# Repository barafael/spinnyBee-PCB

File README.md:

# spinnyBee-PCB
Round PCB for dizzy little gyro on frisbee + WS2812 controlled by an Adafruit ItsyBitsy M4

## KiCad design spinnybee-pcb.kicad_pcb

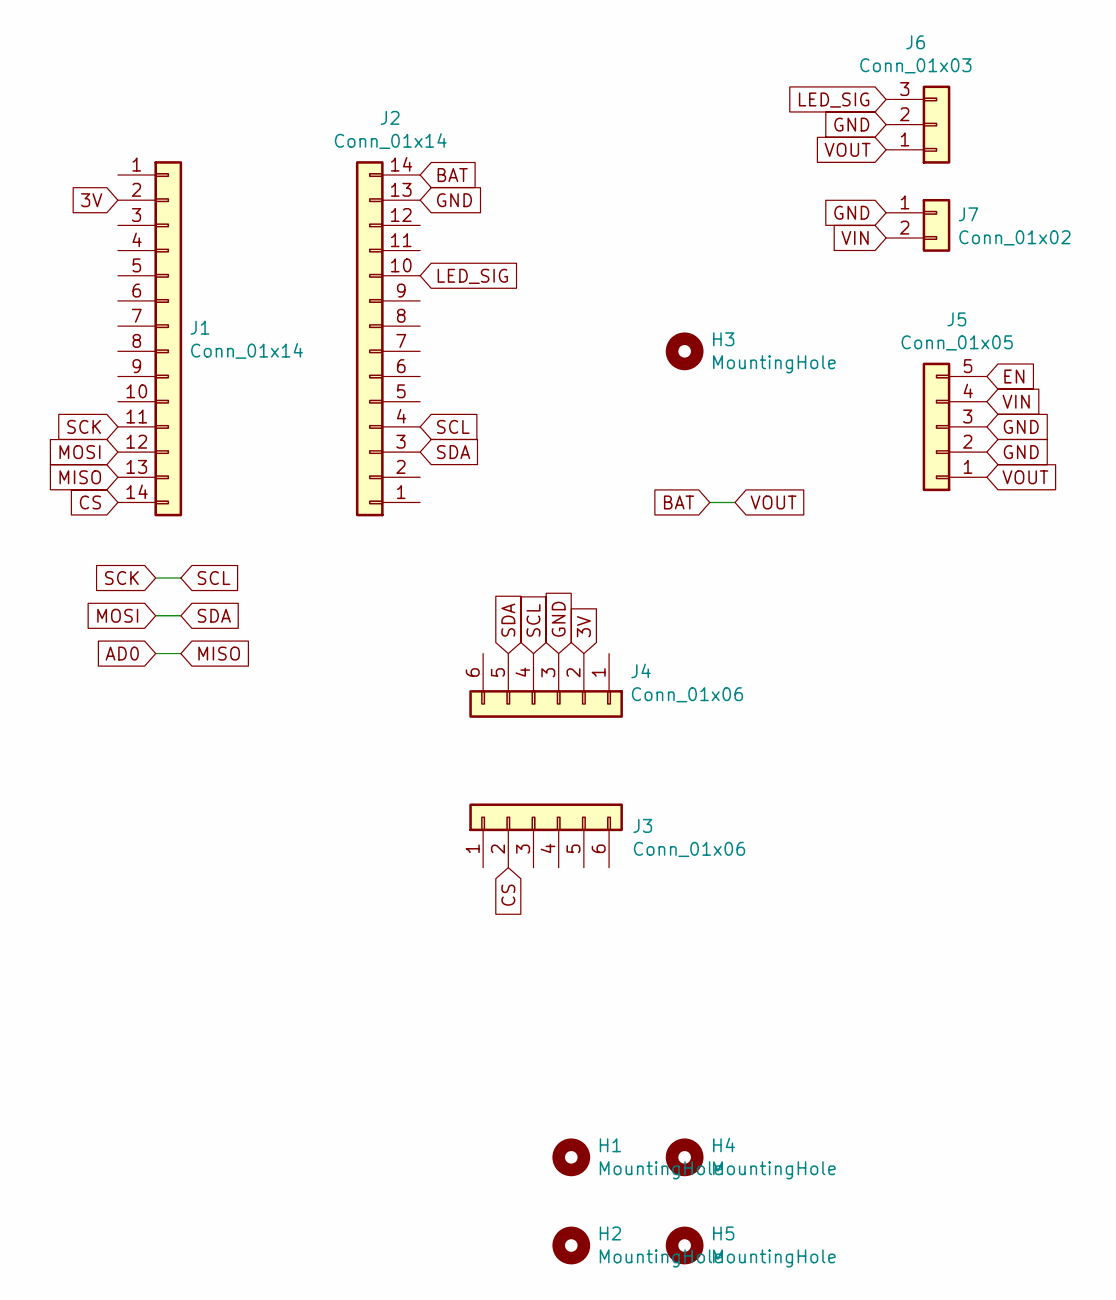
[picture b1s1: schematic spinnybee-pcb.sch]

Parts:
H1, H2, H3, H4, H5: MountingHole; MountingHole_3.2mm_M3
J1, J2: Conn_01x14; PinHeader_1x14_P2.54mm_Vertical
J3, J4: Conn_01x06; PinHeader_1x06_P2.54mm_Vertical
J5: Conn_01x05; PinHeader_1x05_P2.54mm_Vertical
J6: Conn_01x03; PinHeader_1x03_P2.54mm_Vertical
J7: Conn_01x02; PinHeader_1x02_P2.54mm_Vertical

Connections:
3V: J1.2, J4.2
AD0: J1.13
BAT: J2.14, J5.1, J6.1
CS: J1.14, J3.2
EN: J5.5
GND: J2.13, J4.3, J5.2, J5.3, J6.2, J7.1
LED_SIG: J2.10, J6.3
MOSI: J1.12, J2.3, J4.5
SCK: J1.11, J2.4, J4.4
VIN: J5.4, J7.2

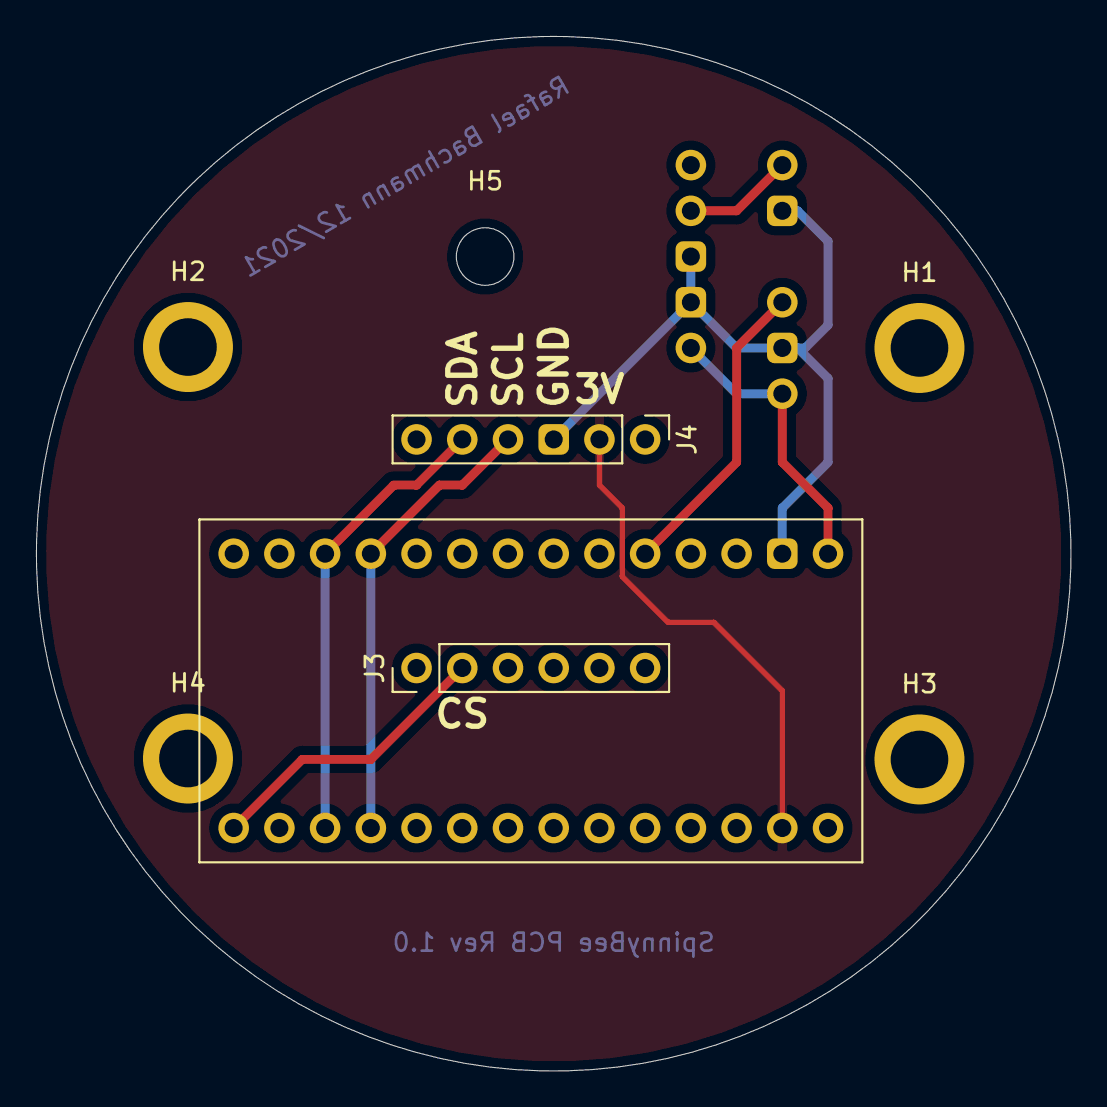
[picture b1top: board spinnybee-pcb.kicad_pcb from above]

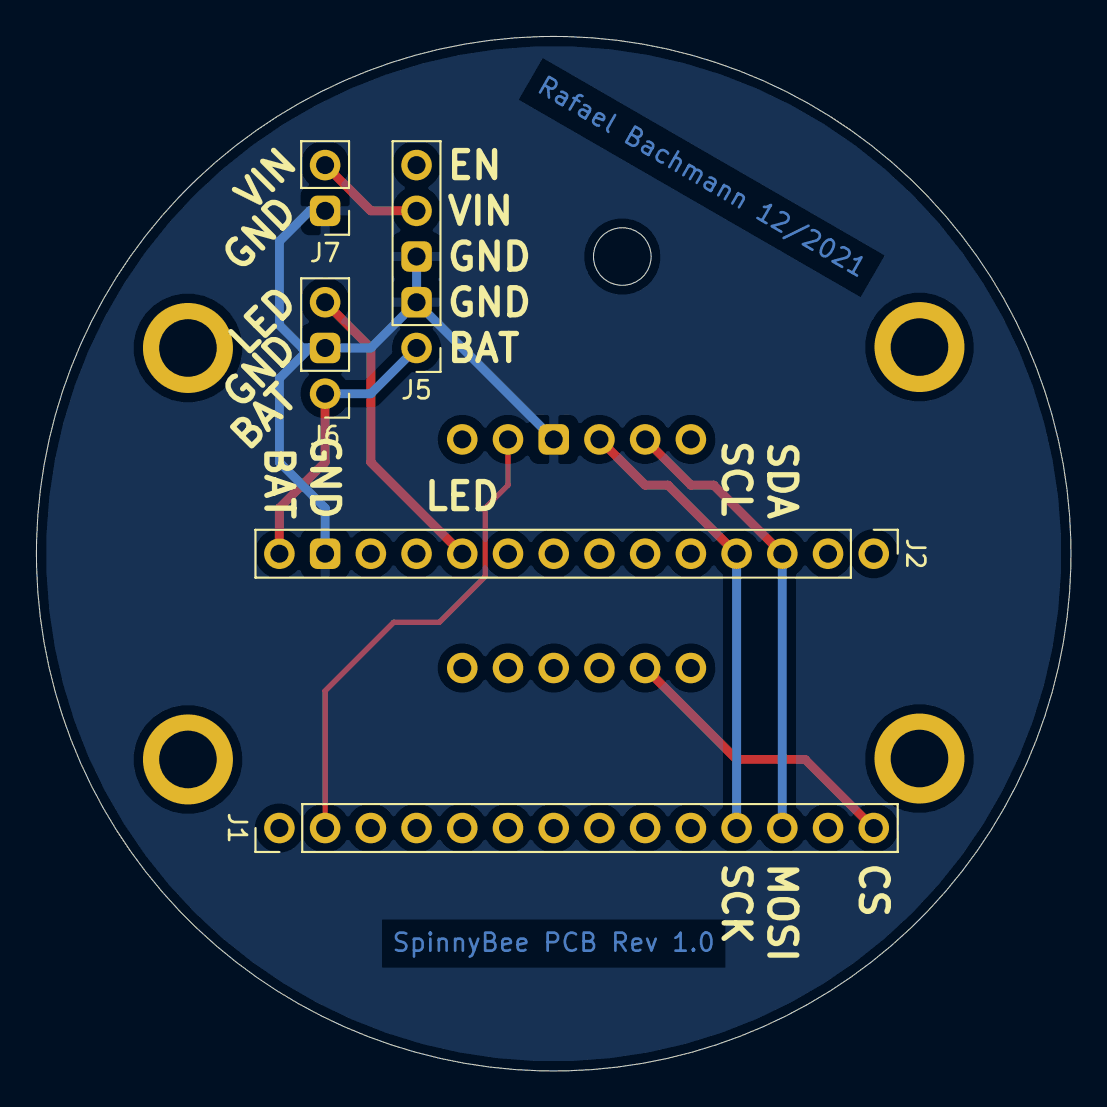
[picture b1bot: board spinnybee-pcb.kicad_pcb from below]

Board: 2 copper layers, 57.5 x 57.5 mm, 12 parts (5 on the bottom side), 8 nets.
